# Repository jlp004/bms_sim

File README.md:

Basic BMS Simulator for connecting and transceiving signals between
* Adafruit CAN PAL
* STM32 G474RE (or other CAN-capable STM32)
* Raspberry Pi

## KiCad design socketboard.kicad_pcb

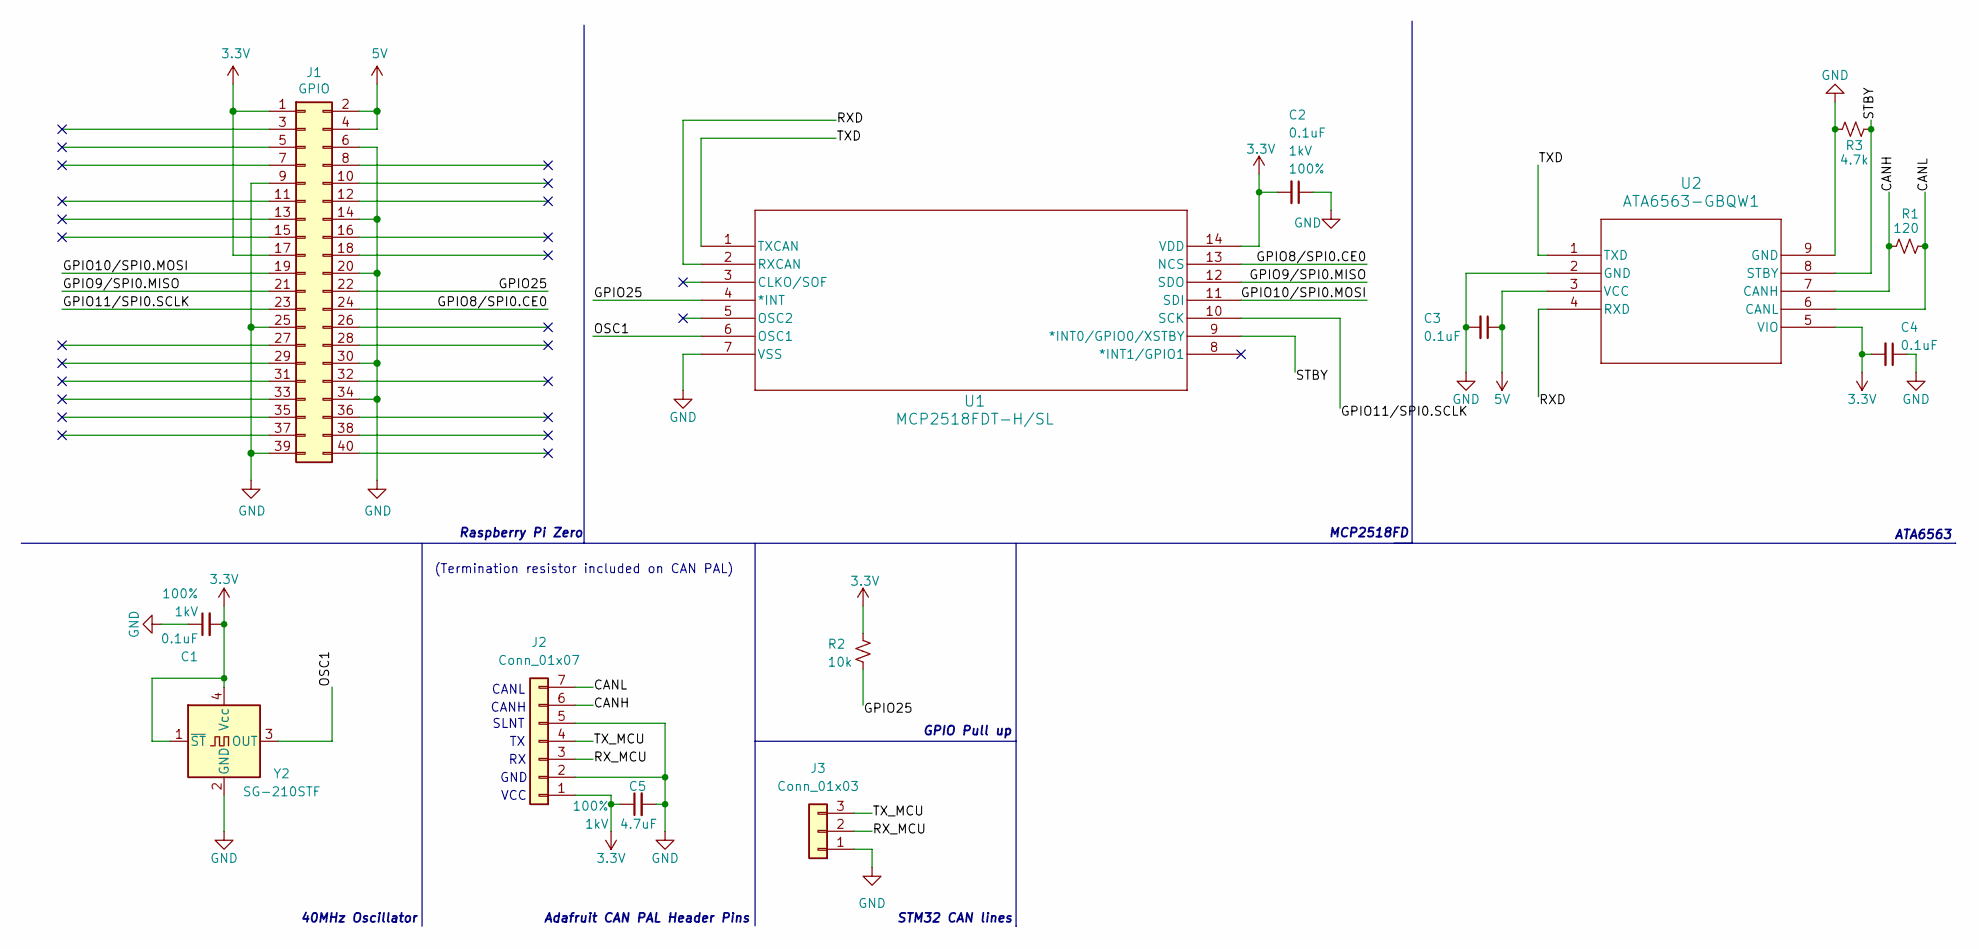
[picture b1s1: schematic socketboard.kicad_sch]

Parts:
C1, C2, C3, C4: 0.1uF; C_0603_1608Metric; Voltage 1kV; Tolerance 100%
C5: 4.7uF; C_0603_1608Metric; Voltage 1kV; Tolerance 100%
J1: GPIO; PinSocket_2x20_P2.54mm_Vertical
J2: Conn_01x07; PinSocket_1x07_P2.54mm_Vertical
J3: Conn_01x03; PinSocket_1x03_P2.54mm_Vertical
R1: 120; R_0603_1608Metric
R2: 10k; R_0603_1608Metric
R3: 4.7k; R_0603_1608Metric
U1: MCP2518FDT-H/SL; SOIC14_150MIL_SL_MCH
U2: ATA6563-GBQW1; VDFN8_3X3_GB-Q8B_MCH
Y2: SG-210STF; Oscillator_SMD_SeikoEpson_SG210-4Pin_2.5x2.0mm

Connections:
3.3V: C1.2, C2.2, C4.2, C5.1, J1.1, J1.17, J2.1, R2.2, U1.14 (VDD), U2.5 (VIO), Y2.1 (~ST), Y2.4 (Vcc)
5V: C3.1, J1.2, J1.4, U2.3 (VCC)
/CANH: J2.6, R1.2, U2.7 (CANH)
/CANL: J2.7, R1.1, U2.6 (CANL)
/GPIO8/SPI0.CE0: J1.24, U1.13 (NCS)
/GPIO9/SPI0.MISO: J1.21, U1.12 (SDO)
/GPIO10/SPI0.MOSI: J1.19, U1.11 (SDI)
/GPIO11/SPI0.SCLK: J1.23, U1.10 (SCK)
/GPIO25: J1.22, R2.1, U1.4 (*INT)
/OSC1: U1.6 (OSC1), Y2.3 (OUT)
/RXD: U1.2 (RXCAN), U2.4 (RXD)
/RX_MCU: J2.3, J3.2
/STBY: R3.1, U1.9 (*INT0/GPIO0/XSTBY), U2.8 (STBY)
/TXD: U1.1 (TXCAN), U2.1 (TXD)
/TX_MCU: J2.4, J3.3
GND: C1.1, C2.1, C3.2, C4.1, C5.2, J1.6, J1.9, J1.14, J1.20, J1.25, J1.30, J1.34, J1.39, J2.2, J2.5, J3.1, R3.2, U1.7 (VSS), U2.2 (GND), U2.9 (GND), Y2.2 (GND)

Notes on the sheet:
Raspberry Pi Zero
SLNT
MCP2518FD
(Termination resistor included on CAN PAL)
Adafruit CAN PAL Header Pins
GPIO Pull up
40MHz Oscillator
CANH
CANL
GND
STM32 CAN lines
VCC
ATA6563

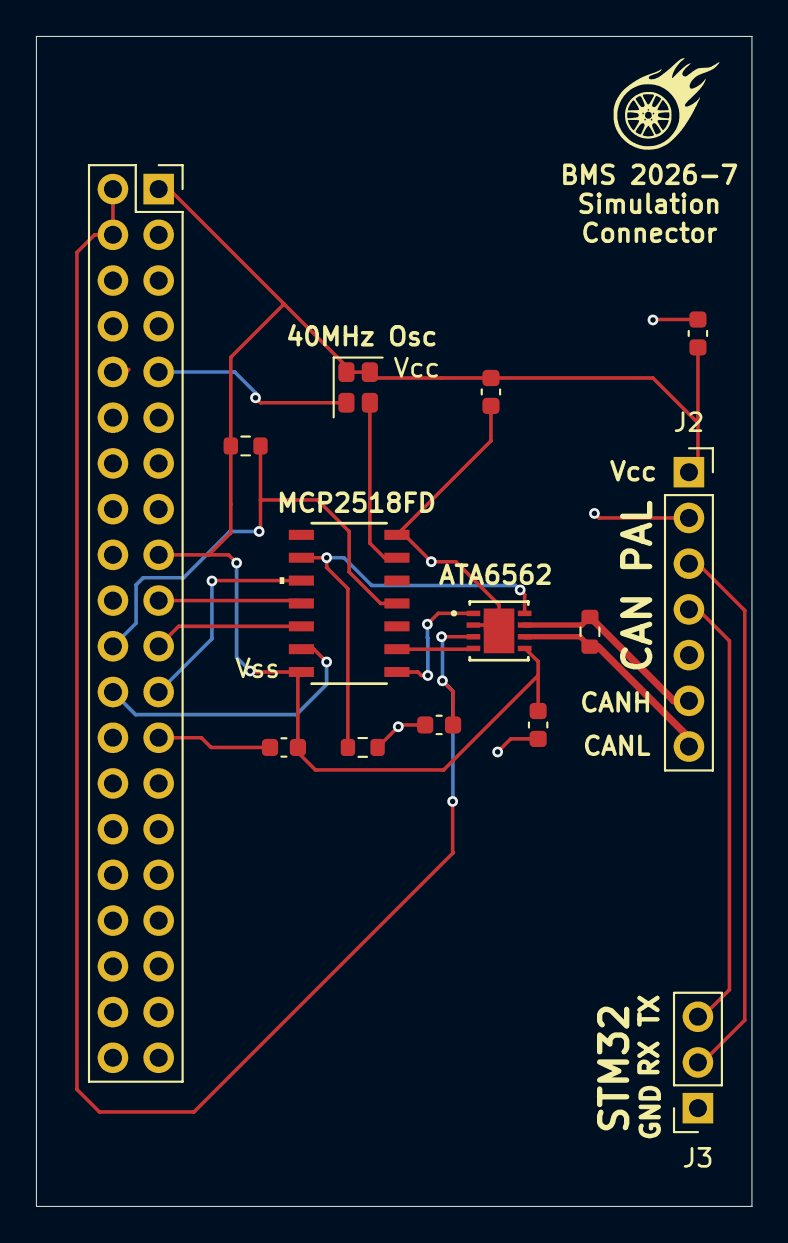
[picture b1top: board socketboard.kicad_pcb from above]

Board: 2 copper layers, 39.8 x 65.0 mm, 14 parts (0 on the bottom side), 16 nets.

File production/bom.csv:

Designator,Footprint,Quantity,Value,LCSC Part #
"C1, C2, C3, C4",0603,4,0.1uF,
C5,0603,1,4.7uF,
J1,PinSocket_2x20_P2.54mm_Vertical,1,GPIO,
J2,PinSocket_1x07_P2.54mm_Vertical,1,Conn_01x07,
J3,PinSocket_1x03_P2.54mm_Vertical,1,Conn_01x03,
R1,0603,1,120,
R2,0603,1,10k,
R3,0603,1,4.7k,
U1,SOIC14_150MIL_SL_MCH,1,MCP2518FDT-H/SL,
U2,VDFN8_3X3_GB-Q8B_MCH,1,ATA6563-GBQW1,
Y2,Oscillator_SMD_SeikoEpson_SG210-4Pin_2.5x2.0mm,1,SG-210STF,
